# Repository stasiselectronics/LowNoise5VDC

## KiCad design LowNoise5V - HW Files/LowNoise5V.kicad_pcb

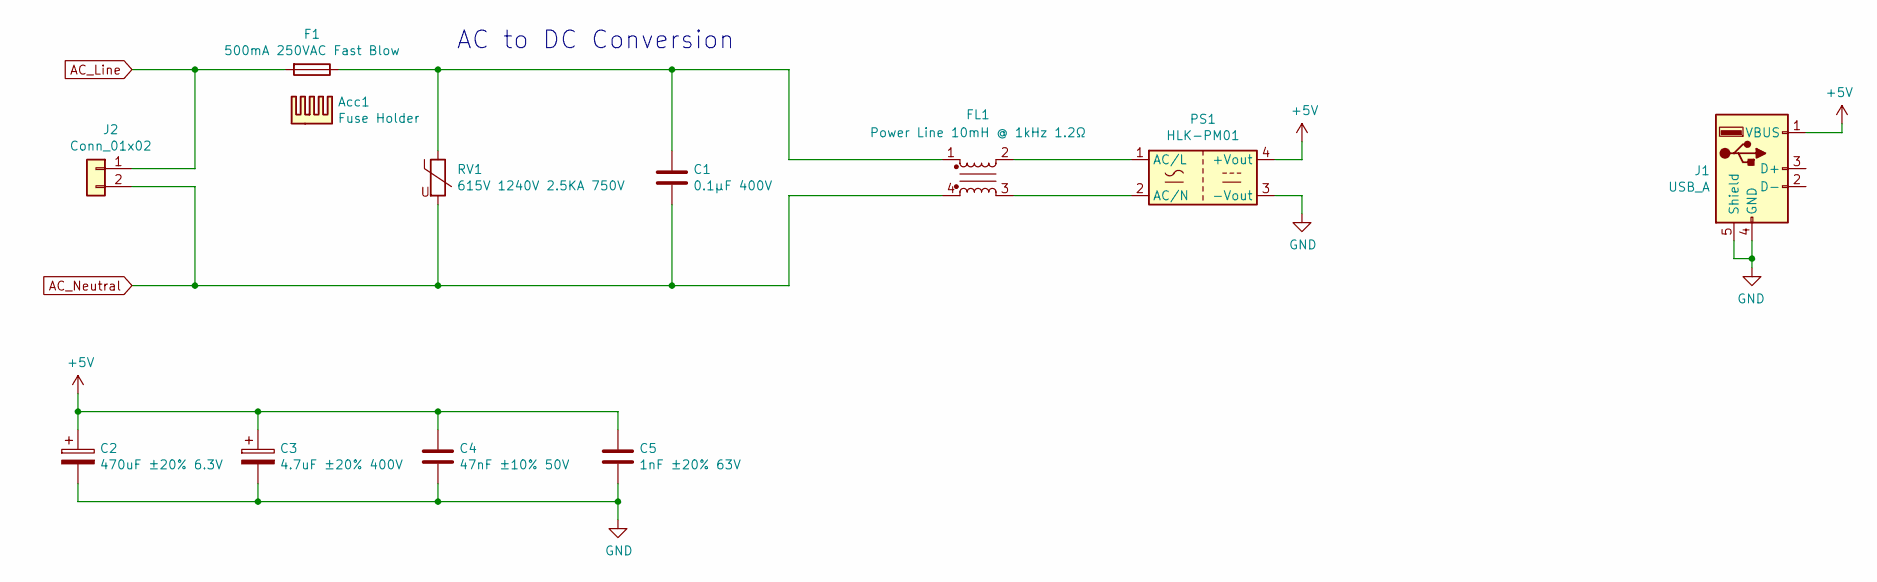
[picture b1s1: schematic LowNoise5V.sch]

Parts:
Acc1: Fuse Holder; FuseHolder; Part 1 MF HONGJU
C1: 0.1µF 400V; C_Rect_L10.0mm_W4.0mm_P7.50mm_MKS4; Part 1 MF Tongfeng
C2: 470uF ±20% 6.3V; CP_Radial_D6.3mm_P2.50mm; Part 1 MF Rubycon
C3: 4.7uF ±20% 400V; CP_Radial_D6.3mm_P2.50mm; Part 1 MF AISHI(Aihua Group)
C4: 47nF ±10% 50V; C_Disc_D6.0mm_W2.5mm_P5.00mm; Part 1 MF Dersonic
C5: 1nF ±20% 63V; C_Disc_D6.0mm_W2.5mm_P5.00mm; Part 1 MF TORCH
F1: 500mA 250VAC Fast Blow; Part 1 MF Xucheng Elec
FL1: Power Line 10mH @ 1kHz 1.2Ω; EMI Choke; Part 1 MF FH(Guangdong Fenghua Advanced Tech)
J1: USB_A; USB_A_Molex_67643_Horizontal; Part 1 MF Molex
J2: Conn_01x02; TerminalBlock_bornier-2_P5.08mm
PS1: HLK-PM01; Converter_ACDC_HiLink_HLK-PMxx; Part 1 MF HI-LINK
RV1: 615V 1240V 2.5KA 750V; C_Rect_L9.0mm_W9.8mm_P7.50mm_MKT; Part 1 MF Hongzhi Elec

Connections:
+5V: C2.1, C3.1, C4.1, C5.1, J1.1 (VBUS), PS1.4 (+Vout)
AC_Line: F1.2, J2.1
AC_Neutral: C1.2, FL1.4, J2.2, RV1.2
GND: C2.2, C3.2, C4.2, C5.2, J1.4 (GND), J1.5 (Shield), PS1.3 (-Vout)
unnamed: C1.1, F1.1, FL1.1, RV1.1
unnamed: FL1.2, PS1.1 (AC/L)
unnamed: FL1.3, PS1.2 (AC/N)

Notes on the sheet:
AC to DC Conversion

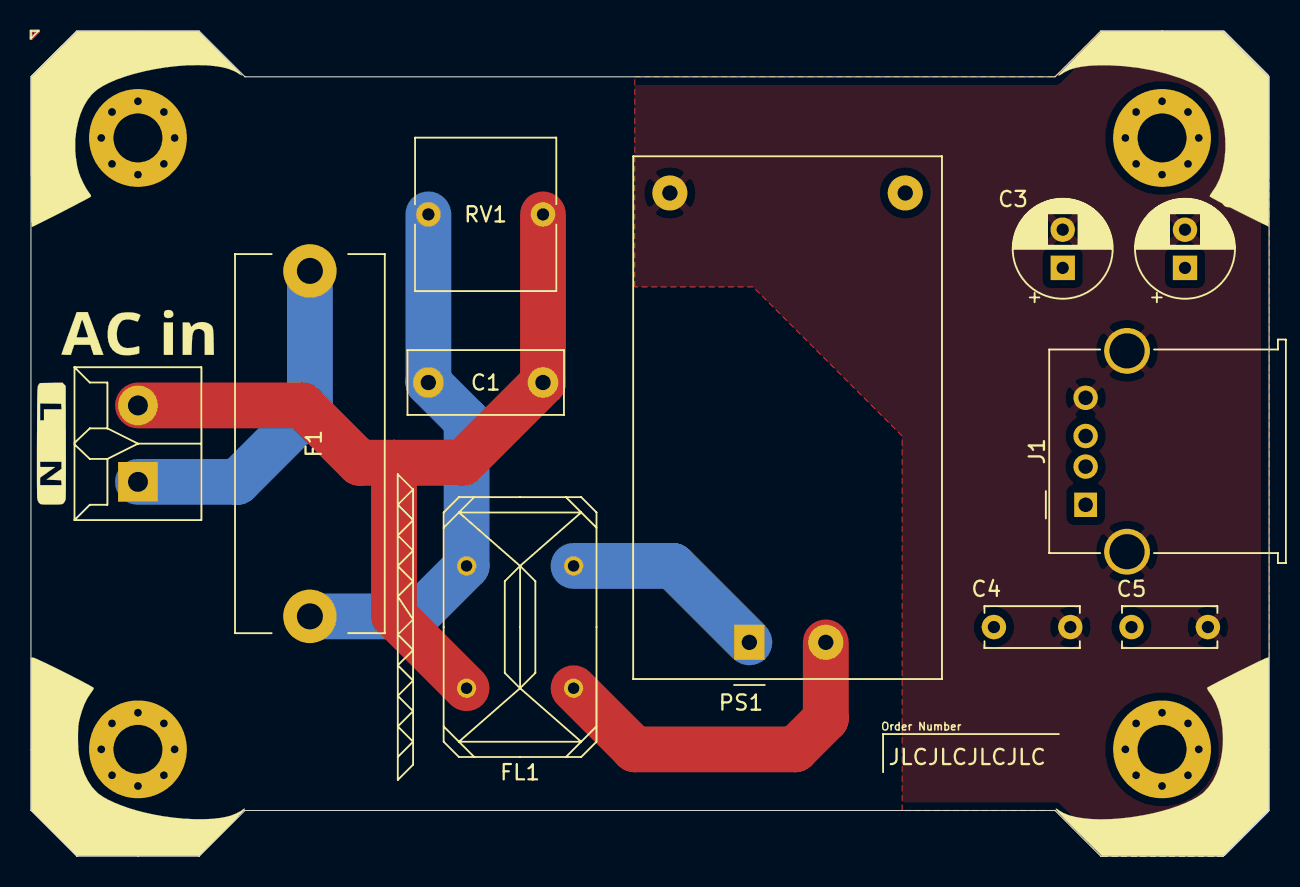
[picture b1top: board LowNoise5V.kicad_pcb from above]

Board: 2 copper layers, 81.0 x 54.0 mm, 11 parts (0 on the bottom side), 7 nets.

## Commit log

2021-03-15 remove schematic used for importing components
2021-03-15 Update AC side components with part info
2021-03-15 Add DC component part info
2021-03-15 finalize component part selection and populate some footprints
2021-03-15 Add footprint and symbol library
2021-03-15 Customize footprints and place more components
2021-03-15 move around components
2021-03-15 move around symbols
2021-03-18 Add same screw terminal as in HotPlatController
2021-03-18 Finalize Routing
2021-03-19 add fiduciary mark to silkscreen
2021-03-19 Finalize Artwork
2021-03-19 Create Fab files
2021-03-19 Add JLCPCB order number location
2021-03-19 Update Fab Files for missing order number location
2021-03-21 Finalize design files for release
2021-04-17 Add 3D model
2021-04-17 Add Enclosure files
2021-04-17 add dimensions
